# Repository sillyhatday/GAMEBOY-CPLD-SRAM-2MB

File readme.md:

# GAMEBOY-CPLD-SRAM-2MB

>[!WARNING]
>Current circuit board revision does not include support for the MAX7000 or ATF150x CPLD without bodges.

## Introduction:

This is my take of a CPLD based flash cart for the Gameboy.

The whole project is based from Alex's project from years back. Without that project, I would never have picked this up and spend my time figuring out how to work with CPLDs. I am not a programmer and do not claim to be. Picking up Alex's code I can see how things work with my previous knowledge of how carts operate.

This version uses SRAM like Alex's did originally. As much as I love using FRAM to bring this old technology towards the modern age, it is technically not compatible due to timing and different glue logic requirments. Not to mention it's really expensive new, China sells cheap factory rejects, and on the whole it's a pain in the ass. Embrace SRAM, it's cheap and available. The battery life is not an issue as people want to think, my original Pokemon Red, Blue and Yellow carts are still using the original batteries with over 3v in them after 28 years.

The newest update has been done with the help of AI. I just wanted to get this thing done so it is off my active project list. Even though AI has helped, I have learned a little bit more about how CPLDs work because of it. In the future I'd like to use the knowledge to do another project.

Some reasons to build this project are:

	+ No need for sourcing a donor cartridge
	+ Multi MBC compatibility
	+ Cheaper to build vs a donor cart (initially not, more made, more saved)
	+ No messing with expensive FRAM or dodgy back ally FRAM

>[!IMPORTANT]
> This project is designed with MBC5 functionality as the main priority. Compatibility with MBC1 is added on top, therefore, compatibility is not guaranteed. Super Mario Land 2 & Zelda: Link's Awakening work here, where they have issues running on a normal MBC5 chip. However, Donkey Kong Land does not work. Maybe one day I can create an MBC1 CPLD mapper.

>[!NOTE]
>For updates, see towards the end of the readme

## 🟦 Project State:

### :green_circle: Done

	- Get a cartridge that works well enough
	- Make the Altera 3032A & 3064A both work
	- Fix SRAM problems with MAX7000 and edge case MAX3000
	- Fix this readme after half updating and rage quitting. Remove V2.0 PCB pics.
	- Write draft of instructions for programming Atmel chips

### :yellow_circle: In Progress

	- Do some power tests of carts I have built so far.

### :white_circle: To Do

	- Test flashing Atmel chips in circuit
	- Design some hardware to flash Atmel chips in circuit
	- Update PCB to include solder jumper for different CPLD families.
	- Some issues with SRAM in FlashGBX with Atmel 1502A. Check hardware over & adjust WinCUPL settings.

## 🟨 Prerequisites

	* The full components parts list and cart PCB
	* (Optional) JTAG adaptor PCB
	* Altera USB Blaster or FT232 for JTAG (cheap clones work)
	* Windows PC with Quartus II Programmer, Quartus II Web Edition or OpenOCD
	* GBxCart and related software
 	* Modified Gameboy cart shell or (optional) 3D printed Game Gear cart adaptor
	* Equipment to solder tiny SMD components
	* Skills to solder tiny SMD components reliably

## 🔌 CPLD Information

>[!TIP]
>Information on chosing a CPLD <br>
>[ALTERA PROGRAMMING GUIDE](AlteraProgrammingGuide.md) <br>
>[ATMEL PROGRAMMING GUIDE](AtmelProgrammingGuide.md) <br>
>[CPLD POWER USAGE](CartPowerUse.md) <br>

Prices vary, these are typical.

| Model | Cost x1 | Vendor |
| ----- | ------- | ------ |
| 3032A: | €1.16 | Aliexpress |
| 3064A: | €1.60 | Aliexpress |
| 7032S: | €1.85 | Aliexpress |
| 1504A: | €1.97 | Mouser |

Depending on the model, the AP2127K-3.3TRG1 may not be needed.

| Model | AP2127K | Jumper |
| ----- | ------- | ------ |
| 3032A | YES | NO |
| 3064A | YES | NO |
| 7032S | NO | YES |
| 1502A | NO | YES |

## 🟦 Parts List

### Cartridge x1

>[!IMPORTANT]
>When ordering cartridge PCBs, make sure to choose 0.8mm thickness and gold plating. <br>
>Altera MAX3000 & MAX7000 CPLDs are obselete and only found on Aliexpress. I suggest the 3032A. (MAX7000 is a relic at this point). <br>
>If ordering MAX7000, get the S version, otherwise throw your money in a fire. Eg, EPM7032S <br>
>Atmel ATF150x parts can be bought new from reputable sellers. However they are trickier to program for the average person. <br>
>Order FRAM from Aliexpress & eBay at your own risk, they are known to be ***extremely*** unreliable. <br>

| Part No. | Package | Qty |
| -------- | ------- | --- |
| 29F016 | TSOP48 | 1 |
| IS62C256* | SOIC28 | 1 |
| CPLD** | TQFP44 | 1 |
| AP2127K-3.3TRG1*** | SOT23-5 | 1 |
| TPS3613-01DGSR | 10VSSOP | 1 |
| 2N7002 | SOT23 | 1 |
| Cap 100nF | 0603 | 5 |
| Cap 1uF | 0603 | 1 |
| Res 10K | 0603 | 1 |
| Res 49K9 | 0603 | 1 |
| Res 130K | 0603 | 1 |
| Bat Holder | AliExp | 1 |

**Other alternatives include, but are not limited to: AS6C6256, CY62256, R1LP5256. <br>
***EPM3064A, EPM3032A, EPM7064S, EPM7032S, ATF1504A or ATF1502A. <br>
****See CPLD info*

### JTAG Adaptor

| Part No. | Qty |
| -------- | --- |
| DS Lite Cart Conn | 1 |
| USB C USB4125 | 1 |
| Pin Headers | 2x5-P2.54mm |
| GG Adaptor or Shell | 1 |
| USB Blaster | 1 |

>[!TIP]
>Link to [Game Gear Adaptor](https://www.thingiverse.com/thing:5830799)

## Build Photos

**Different CPLD** <br>

## Update June 2026

I've picked this back up again when I found a PCB laying about. I had to wonder if AI was good enough now to help improve things. It is fortunately.

The previous update I was naive to think programming in C++ was anything like Verilog. I mean it is, but the device being programmed works so differently to other CPU based systems.

The issue that has been plaguing the 7032S & 1504A, is the save RAM functionality. Games would not save, or correctly use the cartridge as work RAM. This was on the Gameboy and cart readers. I tested this over a few carts and the first one kinda worked. It was flaky but saving, yet only on the GB and not the cart reader. There worst problem is that this problem crept into some of the 3032A and 3064A carts also.

This code refactor seems to have fixed all these problems, not only the MAX3000 but the MAX7000 also. As of now, the ATF1504 is untested. I am hopeful that it will work also. Programming those is more complex and I've since forgotten how to do it.

The smaller EPM3032A, EPM7032S & ATF1502 with 32 macro cells are now more than big enough to fit the program, no longer is it so tight. This is thanks to removing the 128KB RAM functionality, reducing the amount of registers required to address that has gained a lot of space. Additional code can be added for more functionality such as moving the FRAM gate logic into the CPLD and making it user programmable with a solder bridge on the PCB.

This is all very nice as the smaller chips tend to use less power than the larger counterparts, even though they use the same quantity of macro cells. I'll add more detailed information on the changes in its own readme.

When the Atmel part is confirmed working, I'll update the rest of the readme to walk though programming those. Ideally the PCB could use a revision to add the FRAM mode jumper and a jumper to bypass the 3.3v regulator when using the MAX7000 and ATF15xx chips. Again, I'll get to that when testing is complete.

## Firmware Versions

| Version | Status | Notes |
| ------- | ------ | ----- |
| V1.0.0  | Initial | Original code from Alex's blog |
| V1.0.1  | Fix | Removed internal FRAM chip select logic to lower cartridge power consumption 1 to 3% |
| V2.0.0  | Fix | Changed project compiler settings to lower cartridge power consumption 36 to 41% |
| V3.0.0  | Current | AI helper to teach me and structure code better. Use of macro cells more efficient. Logic split into smaller sections. More reliable, cleaner code, better output waveforms (I need to confirm that). |

## 🩷 Links

🔧 Driver Install: https://www.terasic.com.tw/wiki/Intel_USB_Blaster_Driver_Installation_Instructions <br>
⬇️ Driver Download: https://github.com/sudhamshu091/USB-Blaster-Driver-for-DE10-lite <br>
🖨️ Game gear Adaptor: https://www.thingiverse.com/thing:5830799 <br>
⏬ Alt Link Quartus: https://archive.org/details/quartus-iiprogrammer-and-signal-tap-ii-13.1.0.162.7z <br>
🛍️ Inside Gadgets Shop: https://shop.insidegadgets.com <br>
📎 Inside Gadgets GitHub: https://github.com/insidegadgets <br>
📷 Inside Gadgets Insta: https://www.instagram.com/inside.gadgets <br>
🖇️ Bytendo Mods GitHub: https://github.com/bytendomods <br>
🐭 Bucket Mouse: https://github.com/Bucket-Mouse <br>
🛒 Natalie Shop: https://nataliethenerd.com/ <br>
🤓 Natalie GitHub: https://github.com/natalie-lang/natalie <br>

Thanks to Xukkorz, Drew, Jamo, Alex, Deceptive Thinker, Natalie the Nerd & anyone else who I may have forgotten.

## License

This work is licensed under a Creative Commons Attribution-ShareAlike 4.0 International License. You are able to copy and redistribute the material in any medium or format, as well as remix, transform, or build upon the material for any purpose (even commercial) - but you must give appropriate credit, provide a link to the license, and indicate if any changes were made.

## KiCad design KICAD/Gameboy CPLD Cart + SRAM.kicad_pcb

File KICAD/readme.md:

I never uploaded the pcb files wtf. I think these are up to date.

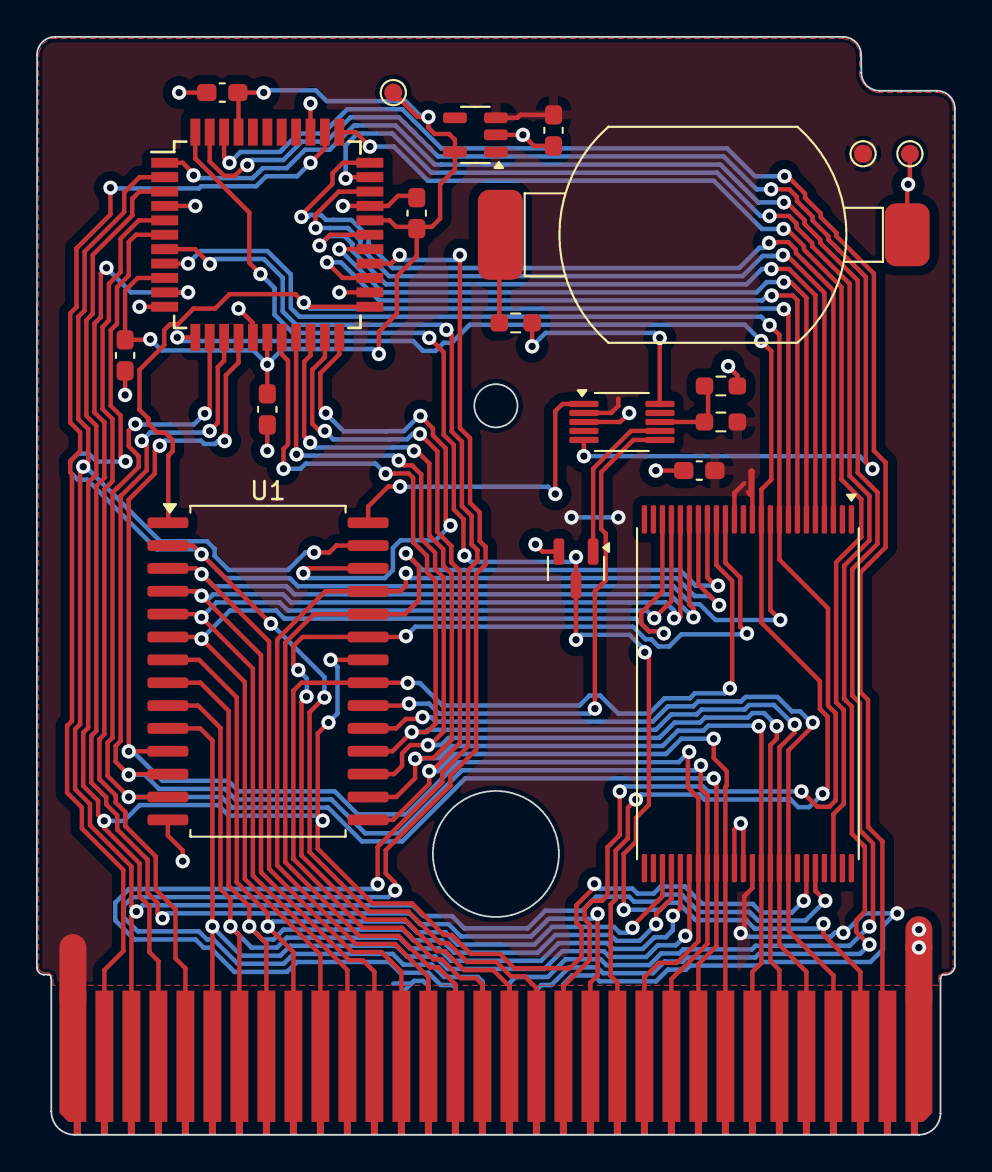
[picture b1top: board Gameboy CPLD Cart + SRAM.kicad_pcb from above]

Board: 2 copper layers, 51.0 x 61.0 mm, 21 parts (1 on the bottom side), 52 nets.

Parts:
BT1: Battery_Cell; CR1616 CLIP IN HOLDER
C1, C2, C3, C5, C7: 100nF; C_0603_1608Metric_Pad1.08x0.95mm_HandSolder
C6: 1uF; C_0603_1608Metric_Pad1.08x0.95mm_HandSolder
J1: Conn_01x06; JTAG Cart Edge Connector
Q1: 2N7002; SOT-23
R1: 10K; R_0603_1608Metric_Pad0.98x0.95mm_HandSolder
R2: 130K; R_0603_1608Metric_Pad0.98x0.95mm_HandSolder
R3: 49K9; R_0603_1608Metric_Pad0.98x0.95mm_HandSolder
TP1: 5V; TestPoint_Pad_D1.0mm
TP2: 3.3V; TestPoint_Pad_D1.0mm
TP3: GND; TestPoint_Pad_D1.0mm
U1: 62C256AL; SOP-28_8.4x18.16mm_P1.27mm
U2: 3032A; TQFP-44_10x10mm_P0.8mm
U3: 29F016; TSOP-I-48_18.4x12mm_P0.5mm
U4: AP2127K; SOT-23-5
U5: TPS3613; MSOP-10_3x3mm_P0.5mm
U?1: CartBus; GameBoy_GamePak_DMG-09_P1.50mm_Edge

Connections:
+3.3V: C1.1, C2.1, C3.2, C6.1, TP2.1, U2.9 (VCC), U2.17 (VCC), U2.29 (VCC), U2.41 (VCC), U4.5 (VOUT)
+5V: C5.1, C7.1, J1.1, R2.1, TP1.1, U3.12 (VCC), U3.14 (RESET), U3.37 (VCC~), U4.1 (VIN), U4.3 (EN), U5.2 (VDD), U?1.1 (VCC)
A0: U1.10 (A0), U3.30 (A0~), U?1.6 (A0)
A1: U1.9 (A1), U3.29 (A1), U?1.7 (A1)
A2: U1.8 (A2), U3.28 (A2), U?1.8 (A2)
A3: U1.7 (A3), U3.27 (A3), U?1.9 (A3)
A4: U1.6 (A4), U3.22 (A4), U?1.10 (A4)
A5: U1.5 (A5), U3.21 (A5), U?1.11 (A5)
A6: U1.4 (A6), U3.20 (A6), U?1.12 (A6)
A7: U1.3 (A7), U3.19 (A7), U?1.13 (A7)
A8: U1.25 (A8), U3.18 (A8), U?1.14 (A8)
A9: U1.24 (A9), U3.17 (A9), U?1.15 (A9)
A10: U1.21 (A10), U3.16 (A10), U?1.16 (A10)
A11: U1.23 (A11), U3.15 (A11), U?1.17 (A11)
A12: U1.2 (A12), U2.6 (I/O), U3.10 (A12), U?1.18 (A12)
A13: U2.8 (I/O), U3.9 (A13), U?1.19 (A13)
A14: U2.10 (I/O), U?1.20 (A14)
A15: U2.12 (I/O), U3.11 (CE), U?1.21 (A15)
AA13: U1.26 (A13), U2.22 (I/O)
CLK: U2.35 (I/O), U?1.2 (CLK~)
CS: U1.20 (~CE), U5.6 (/CEOUT)
D0: U1.11 (I/O0), U2.15 (I/O), U3.31 (D0), U?1.22 (D0)
D1: U1.12 (I/O1), U2.14 (I/O), U3.32 (D1), U?1.23 (D1)
D2: U1.13 (I/O2), U2.13 (I/O), U3.33 (D2), U?1.24 (D2)
D3: U1.15 (I/O3), U2.21 (I/O), U3.34 (D3), U?1.25 (D3)
D4: U1.16 (I/O4), U2.20 (I/O), U3.38 (D4), U?1.26 (D4)
D5: U1.17 (I/O5), U2.19 (I/O), U3.39 (D5), U?1.27 (D5)
D6: U1.18 (I/O6), U2.18 (I/O), U3.40 (D6), U?1.28 (D6)
D7: U1.19 (I/O7), U3.41 (D7), U?1.29 (D7)
GND: BT1.2 (-), C1.2, C2.2, C3.1, C5.2, C6.2, C7.2, J1.6, Q1.2 (S), R3.2, TP3.1, U1.14 (GND), U2.4 (GND), U2.11 (GND), U2.16 (GND), U2.24 (GND), U2.30 (GND), U2.36 (GND), U3.35 (GND), U3.36 (GND), U4.2 (GND), U5.3 (GND), U?1.32 (GND)
MREQ/CS: U2.5 (I/O), U?1.5 (CS)
unnamed: BT1.1 (+), R1.1
unnamed: Q1.1 (G), U5.7 (RST)
unnamed: R2.2, R3.1, U5.8 (SENS)
unnamed: R1.2, U5.10 (VBAT)
RA17: U2.28 (I/O), U3.5 (A17)
RA18: U2.31 (I/O), U3.4 (A18)
RA19: U2.33 (I/O), U3.3 (A19)
RA20: U2.34 (I/O), U3.46 (A20)
RAM_CS: U2.43 (I/O), U5.5 (/CEIN)
RD: U1.22 (~OE), U2.3 (I/O), U3.43 (OE~), U?1.4 (RD)
RRA14: U1.1 (A14), U2.23 (I/O), U3.8 (A14)
RRA15: U2.25 (I/O), U3.7 (A15)
RRA16: U2.27 (I/O), U3.6 (A16)
RST/CS2: Q1.3 (D), U2.44 (I/O), U?1.30 (RST)
SND: U2.42 (I/O), U?1.31 (SND)
TCK: J1.4, U2.26 (I/O/TCK)
TDI: J1.3, U2.1 (I/O/TDI)
TDO: J1.2, U2.32 (I/O/TDO)
TMS: J1.5, U2.7 (I/O/TMS)
Vout: U1.28 (VDD), U5.1 (VOUT)
WR: U1.27 (~WE), U2.2 (I/O), U3.44 (WE), U?1.3 (WR)

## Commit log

2024-12-11 Create readme.md
    Initial commit to save progress
2024-12-11 Update readme.md
    Initial version
2024-12-11 Update readme.md
    added to advantages and disadvantage
2025-05-28 Create License.md
    added license
2025-05-28 Update readme.md
    added license
2025-05-28 Create readme.md
    adding firmware files
2025-05-28 Create readme.md
    adding firmware
2025-05-28 Add files via upload
    3064a firmware
2025-05-28 Add files via upload
    firmware for 3032a
2025-06-01 Update readme.md
    Updated to match FRAM repo
2025-06-01 Create AlteraProgrammingGuide.md
    Added initial programming guide
2025-11-28 Add files via upload
    added raw code. Might be wrong code but whatevs
2025-12-08 Update readme.md
    Update
2026-06-22 Update readme.md
    June 2026 update
2026-06-22 Rename [Alex] GB MBC5-1 Hybrid - R1 (2MB ROM, 32KB FRAM).v to RAW CODE/[Alex] GB MBC5-1 Hybrid - R1 (2MB ROM, 32KB FRAM).v
2026-06-22 Update readme.md
    added progress log
2026-06-23 Update readme.md
    huge update
2026-06-23 Update AlteraProgrammingGuide.md
    Updated to match FRAM git
2026-06-23 Create AtmelProgrammingGuide.md
    Atmel guide added from FRAM git
2026-06-24 Update readme.md
    Brought in line with FRAM version
2026-06-24 Create CartPowerUse.md
    added power use doc
2026-06-25 Create gorboors
